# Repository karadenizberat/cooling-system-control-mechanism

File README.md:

# 🚐 Vehicle Refrigerator Controller (ATmega-based)

This project is designed to control compact refrigerators used in
vehicles. It is based on an ATmega microcontroller and includes:

-   ❄️ Real-time temperature monitoring with an NTC sensor\
-   🔌 Relay control for compressor on/off\
-   📟 OLED display to show ambient and target temperatures\
-   💾 EEPROM storage for saving power state and target temperature\
-   🔘 Button interface to adjust temperature and toggle system on/off

The system continuously monitors ambient temperature and activates the
cooling system when needed. It is ideal for automotive refrigeration
applications requiring reliability and efficiency.

------------------------------------------------------------------------

## 🛠️ Hardware Components

-   ATmega microcontroller (e.g. ATmega328P)
-   NTC Thermistor
-   Relay module (12V/24V depending on compressor)
-   OLED Display (SSD1306 - 128x64)
-   EEPROM (onboard)
-   Push Buttons (Increase / Decrease / Power)
-   Green & Red LEDs for status indication

------------------------------------------------------------------------

## 📁 File Structure

Vehicle-Fridge-Controller/ │ ├── kod/ → Arduino source code (.ino file)
├── eagle/ → Circuit schematic (.sch) & PCB layout (.brd) ├── img/ →
Circuit photos, 3D renders, real setup images └── README.md → Project
description (this file)

------------------------------------------------------------------------

## 🔧 Setup Instructions

1.  Upload the `.ino` code to the ATmega chip using Arduino or ISP
    method.
2.  Wire the components as shown in the schematic (see `eagle/` and
    `img/` folders).
3.  Adjust the target temperature using the buttons.
4.  OLED will show real-time ambient temperature, target, and system
    state.
5.  System state and target temperature are stored in EEPROM, so they
    persist after power-off.

------------------------------------------------------------------------

## 🇹🇷 Proje Açıklaması (Türkçe)

Bu proje, araçlarda kullanılan küçük buzdolaplarını kontrol etmek
amacıyla geliştirilmiştir. ATmega mikrodenetleyici tabanlıdır ve:

-   🌡️ NTC sensörü ile sıcaklık ölçümü\
-   🔁 Röle modülü ile kompresör kontrolü\
-   🖥️ OLED ekran ile sıcaklık ve sistem durumu gösterimi\
-   💾 EEPROM ile sıcaklık ve sistem durumu kaydı\
-   🔘 Butonlarla sıcaklık ayarlama ve sistemi aç/kapatma

Sistem, belirlenen hedef sıcaklığa göre otomatik olarak kompresörü
devreye alır veya durdurur.

------------------------------------------------------------------------

## 📸 Görseller

Aşağıda sistemin gerçek devresi, Eagle şeması ve çalışma görüntüleri yer
alabilir. Bunları `img/` klasöründe saklayın.

------------------------------------------------------------------------

## 🧠 Lisans ve Katkı

Bu proje MIT lisansı altındadır. Dilerseniz fork edip geliştirmelere
katkı sağlayabilirsiniz.

------------------------------------------------------------------------

## 📬 İletişim / Communication

Geliştirici / Developer : \[Berat Karadeniz\]\
GitHub: \[https://github.com/karadenizberat\] LinkedIn:
\[https://www.linkedin.com/in/karadenizberat/\]

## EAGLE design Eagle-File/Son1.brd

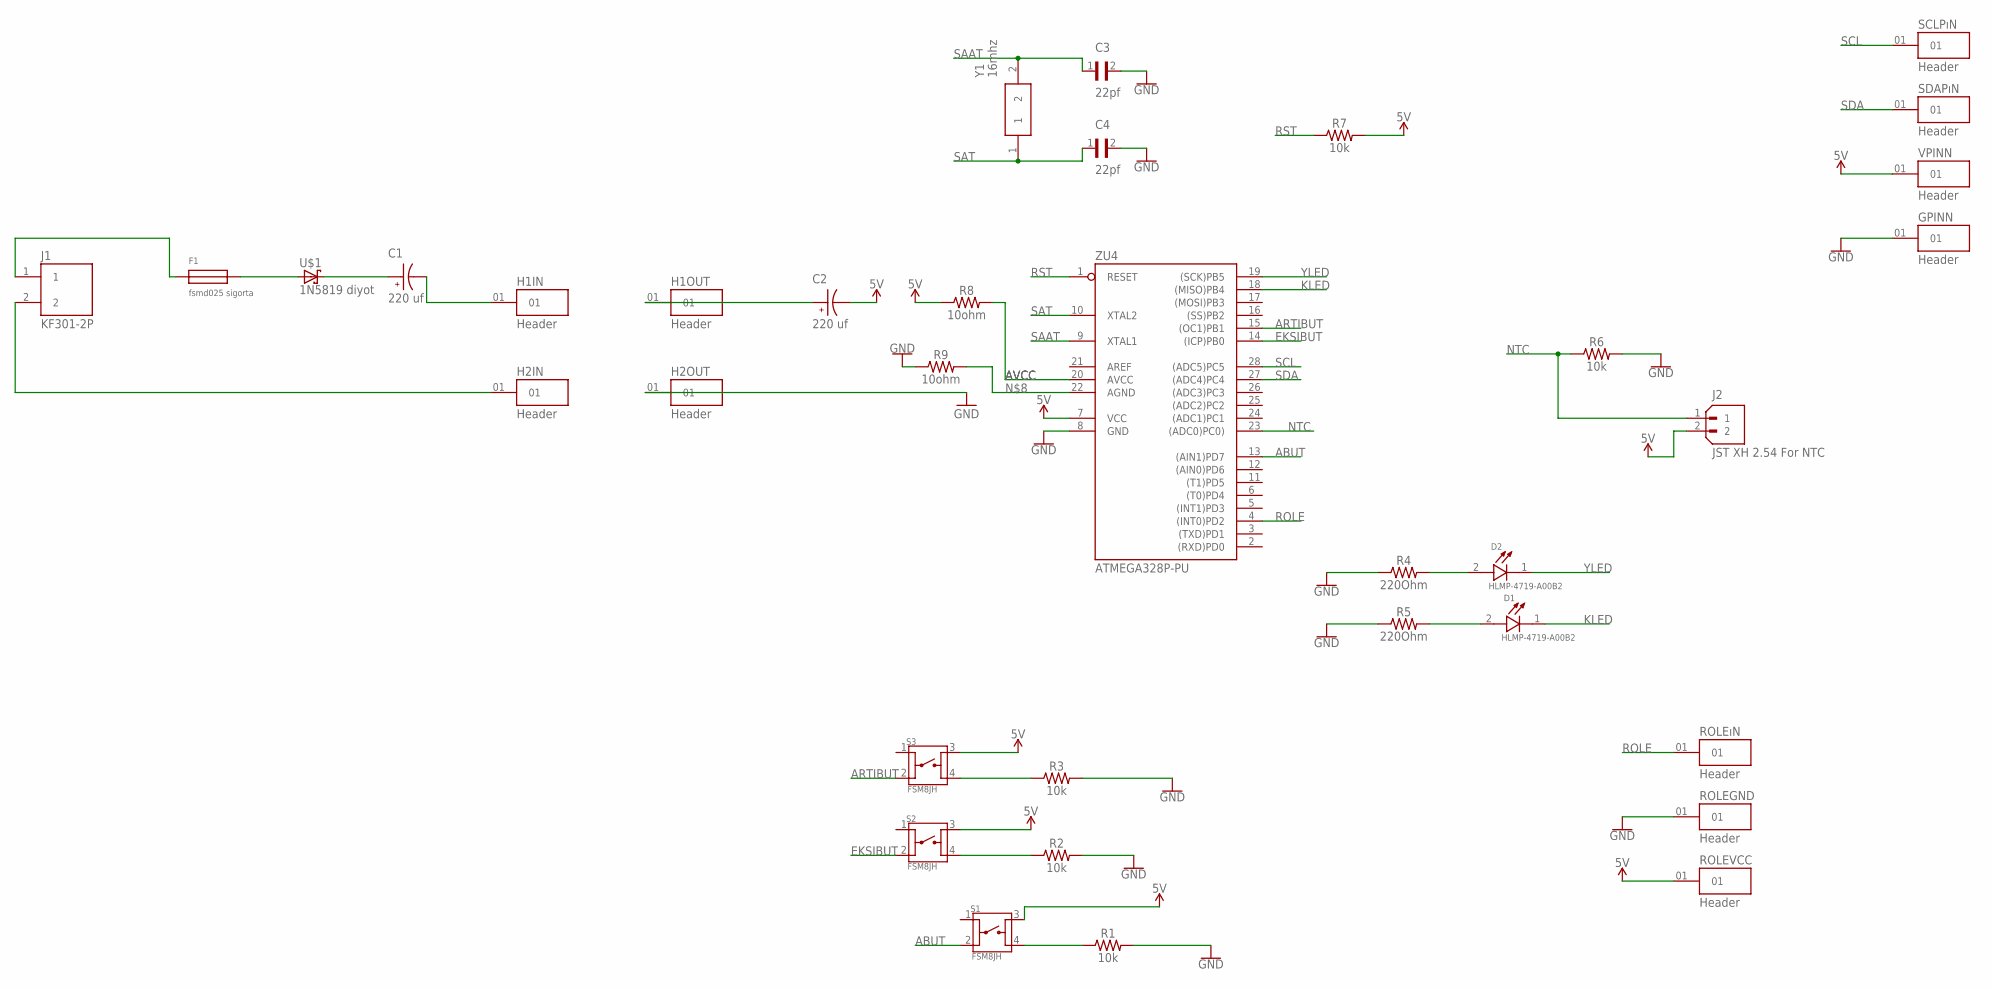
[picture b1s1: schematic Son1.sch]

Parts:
C1, C2: 220 uf; CAP_EEEFP1E101AV
C3, C4: 22pf; CAP_DE21XSA220KN3AX02F
D1, D2: HLMP-4719-A00B2; LEDRD254W47D584H1078
F1: fsmd025 sigorta; 0ZCN
GPINN: Header; SAMTEC_MTMM-101-X-X-S-X
H1IN, H1OUT, H2IN, H2OUT: Header; SAMTEC_MTMM-101-X-X-S-X
J1: KF301-2P; HANDSON_KF301-2P
J2: JST XH 2.54 For NTC; JST_B2B-XH-A(LF)(SN)
R1, R2, R3, R6, R7: 10k; AXIAL-0.3
R4, R5: 220Ohm; AXIAL-0.3
R8, R9: 10ohm; AXIAL-0.3
ROLEGND: Header; SAMTEC_MTMM-101-X-X-S-X
ROLEVCC: Header; SAMTEC_MTMM-101-X-X-S-X
ROLEıN: Header; SAMTEC_MTMM-101-X-X-S-X
S1, S2, S3: FSM8JH; SW_FSM8JH
SCLPıN: Header; SAMTEC_MTMM-101-X-X-S-X
SDAPıN: Header; SAMTEC_MTMM-101-X-X-S-X
U$1: 1N5819 diyot; SOD68
VPINN: Header; SAMTEC_MTMM-101-X-X-S-X
Y1: 16mhz; HC49SLF_1
ZU4: ATMEGA328P-PU; DIL28-3

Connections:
5V: C2.2, J2.2, R7.P$2 (2), R8.P$1 (1), ROLEVCC.01, S1.3, S2.3, S3.3, VPINN.01, ZU4.7 (VCC)
ABUT: S1.2, ZU4.13 ((AIN1)PD7)
ARTIBUT: S3.2, ZU4.15 ((OC1)PB1)
AVCC: R8.P$2 (2), ZU4.20 (AVCC)
EKSIBUT: S2.2, ZU4.14 ((ICP)PB0)
GND: C3.2, C4.2, GPINN.01, H2OUT.01, R1.P$2 (2), R2.P$2 (2), R3.P$2 (2), R4.P$1 (1), R5.P$1 (1), R6.P$2 (2), R9.P$1 (1), ROLEGND.01, ZU4.8 (GND)
KLED: D1.1 (C), ZU4.18 ((MISO)PB4)
unnamed: F1.P$2, U$1.A
unnamed: F1.P$1, J1.1
unnamed: C1.1, U$1.C (K)
unnamed: C1.2, H1IN.01
unnamed: H2IN.01, J1.2
unnamed: C2.1, H1OUT.01
unnamed: R1.P$1 (1), S1.4
unnamed: R9.P$2 (2), ZU4.22 (AGND)
unnamed: R2.P$1 (1), S2.4
unnamed: R3.P$1 (1), S3.4
unnamed: D1.2 (A), R5.P$2 (2)
unnamed: D2.2 (A), R4.P$2 (2)
NTC: J2.1, R6.P$1 (1), ZU4.23 ((ADC0)PC0))
ROLE: ROLEıN.01, ZU4.4 ((INT0)PD2)
RST: R7.P$1 (1), ZU4.1 (RESET)
SAAT: C3.1, Y1.2, ZU4.9 (XTAL1)
SAT: C4.1, Y1.1, ZU4.10 (XTAL2)
SCL: SCLPıN.01, ZU4.28 ((ADC5)PC5)
SDA: SDAPıN.01, ZU4.27 ((ADC4)PC4)
YLED: D2.1 (C), ZU4.19 ((SCK)PB5)

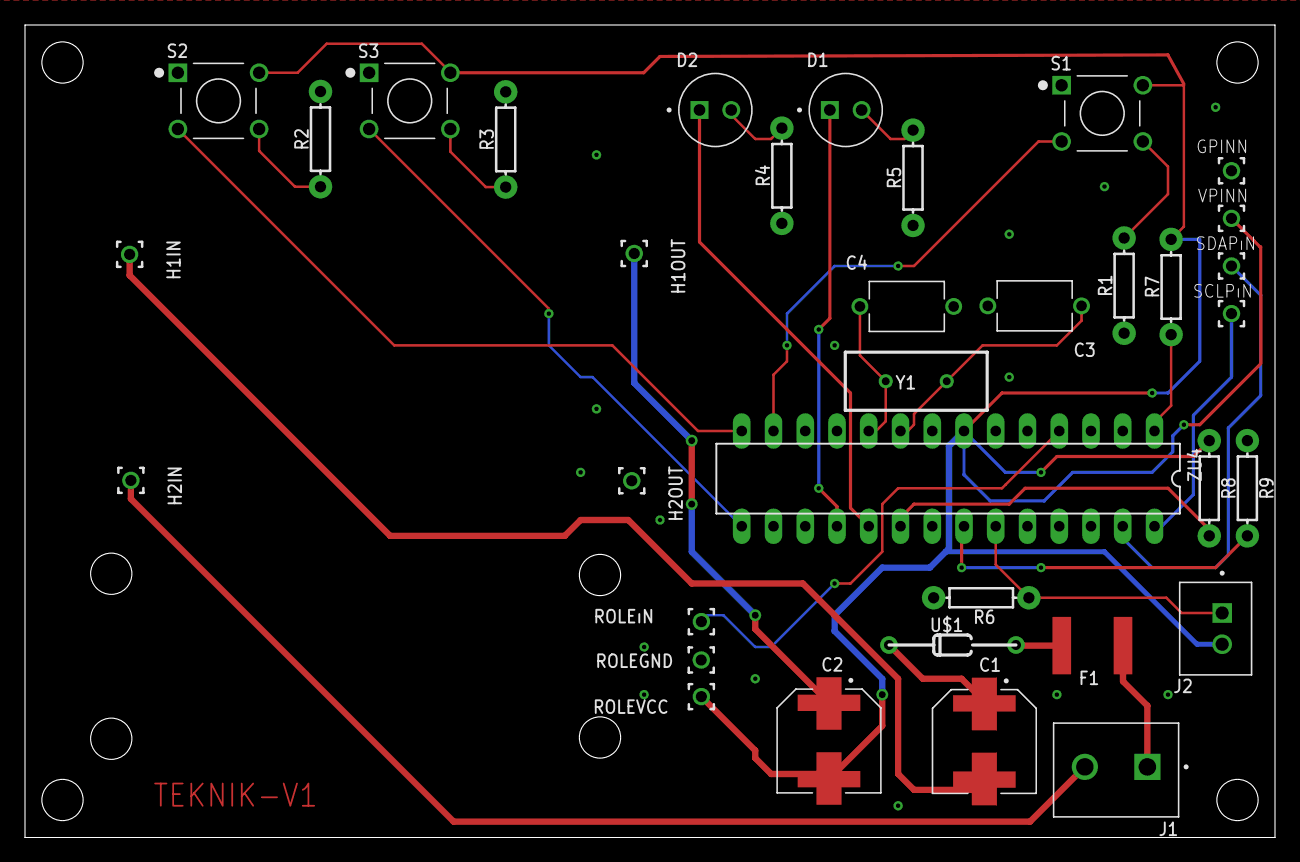
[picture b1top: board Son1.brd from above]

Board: 2 copper layers, 100.0 x 65.0 mm, 35 parts (0 on the bottom side), 27 nets.

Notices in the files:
parts and their libraries:
SparkFun-Resistors: Licensing: Creative Commons ShareAlike 4.0 International - https://creativecommons.org/licenses/by-sa/4.0
